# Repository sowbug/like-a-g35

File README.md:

Like A G35
==========

An alternate driver for GE Christmas lights that's an Arduino shield. Based on the 
[G35Arduino project](https://github.com/sowbug/G35Arduino). These instructions are 
for the G35 side of the board, built as of [tag v0.1](https://github.com/sowbug/like-a-g35/zipball/v0.1).

BOM
===

* The board. Have it manufactured by [OSH Park](http://oshpark.com/).
* A micro-USB connector, FCI part [10118193-0001LF](http://www.mouser.com/ProductDetail/FCI/10118193-0001LF/?qs=%2fha2pyFadujdGYiRLwYbSOKALiSo%252bepJVRcIj9hkdZjVBFUo3HGQQw%3d%3d).
* At least one [5.08MM 3-pin terminal block](http://www.mouser.com/ProductDetail/TE-Connectivity-AMP/282837-3/?qs=sGAEpiMZZMvlX3nhDDO4AEiipl7BG01uQiHyL2Oob2I%3d). The green things with screws.
* A bunch of snappable pin headers -- enough to make the usual Arduino 8/8/6/6 combo.
* Recommended: an Arduino, both for using with the shield, and during assembly as a frame for getting
the header pins straight.

Initial Usage
=============

1. Clone [G35Arduino](https://github.com/sowbug/G35Arduino) following the placement instructions there.
1. Fire up your Arduino IDE.
1. Change any of the examples to use pin 8 for the first strand, pin 9 for the second strand, and pin 10
if you're a big spender and have three G35 strands.
1. Program your Arduino.
1. Plug in the shield. Look for smoke. If you're more careful than I am, confirm that 5V is reading 5 volts,
GND is reading zero volts, and Data on the G1 header is putting out a digital signal.
1. Hook up the first strand of lights to the three-terminal header marked G1. Right before you cut off the
controller, as you were looking at the first light you saw +/D/-, left to right. See the
[V+/D/V- diagram](http://www.deepdarc.com/2010/11/27/hacking-christmas-lights/). Hook up + to 5V, the
middle wire to Data, and - to GND.
1. If you still have your Arduino plugged into your computer, by now you should be seeing at least the test
pattern on your strand. If not, check your wiring and assembly.

Production Usage
================

* The reason there is a USB connector on the shield is that the Arduino's power is limited to 500mA, or
else you risk blowing its polyfuse. Even a single G35 strand can use more than an amp. But the shield's USB
connector is a *direct* connection to the light power lines. So as long as you can find a power adapter
that fits the micro-USB plug (should be easy; lots of power adapters these days have type-A USB) and
provides regulated 5V, you can pump as much current as you want into this shield (it'll also power the
Arduino, of course). *BEWARE* that in exchange for this freedom, you can easily kill your lights and your
Arduino. You *must* provide *a regulated 5-volt supply*. Not 4.5, not 6, not 9, not 12. I don't care if your
7.5-volt supply worked fine with your Arduino. If you hook it up to this USB socket, all your hardware will
die and you might burn down your house.
* I've soldered the stranded copper wire of my lights so that they don't tarnish too much over the winter.

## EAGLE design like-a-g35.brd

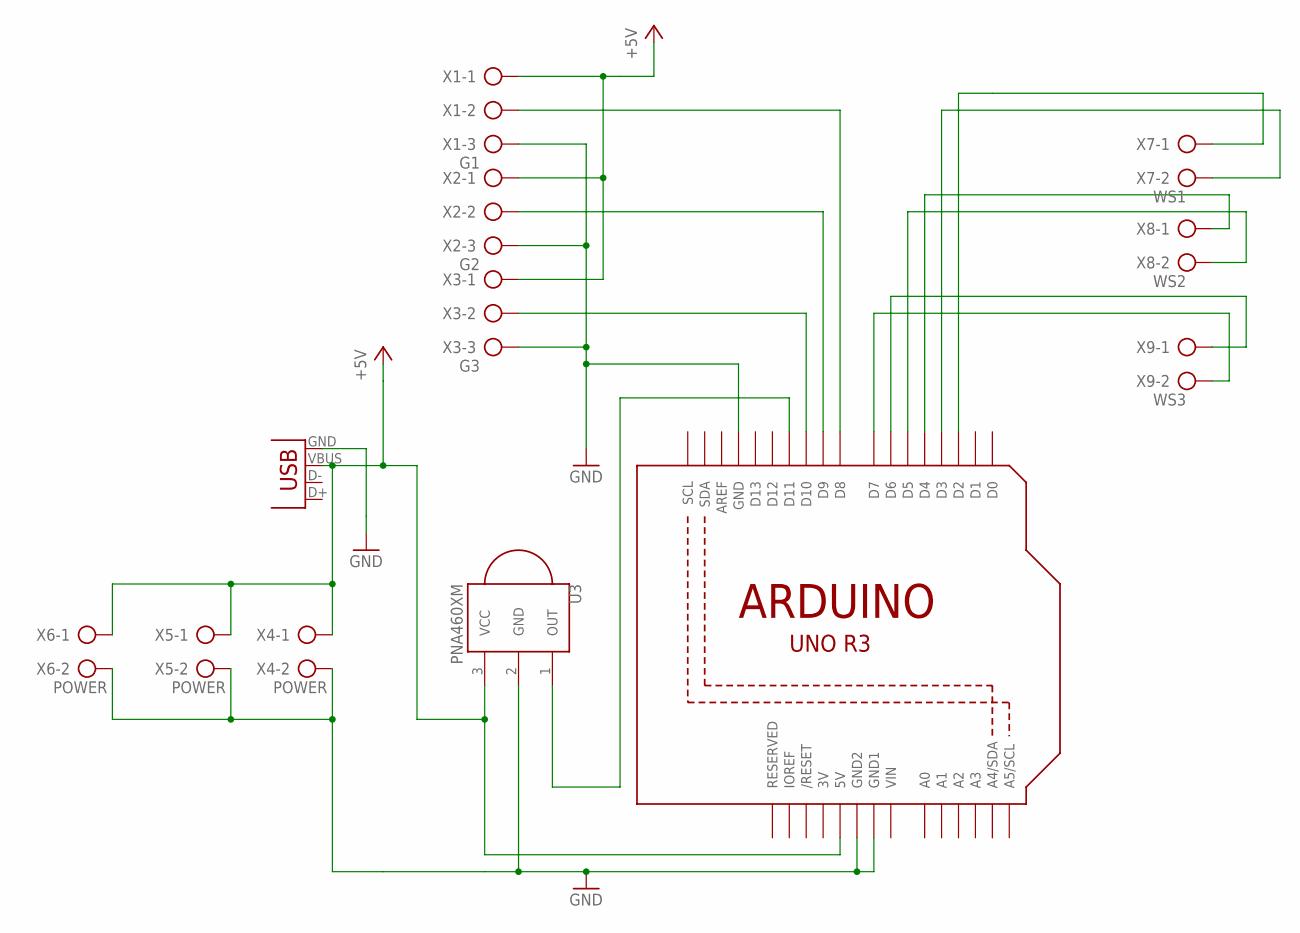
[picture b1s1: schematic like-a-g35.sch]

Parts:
U1: ARDUINOR3-DIMENSION; ARDUINOR3
U2: FCI_8193_MICRO_USB; FCI_MICRO_USB_8193
U3: PNA460XM
X1: G1; AK300/3
X2: G2; AK300/3
X3: G3; AK300/3
X4, X5, X6: POWER; AK300/2
X7: WS1; AK300/2
X8: WS2; AK300/2
X9: WS3; AK300/2

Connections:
3V: U1.3V
+5V: U1.5V, U2.VBUS, U3.3 (VCC), X1.1, X2.1, X3.1, X4.1, X5.1, X6.1
CLK1: U1.D3, X7.2
CLK2: U1.D5, X8.2
CLK3: U1.D7, X9.2
DATA1: U1.D2, X7.1
DATA2: U1.D4, X8.1
DATA3: U1.D6, X9.1
GDATA1: U1.D8, X1.2
GDATA2: U1.D9, X2.2
GDATA3: U1.D10, X3.2
GND: U1.GND, U1.GND1, U1.GND2, U2.GND, U3.2 (GND), X1.3, X2.3, X3.3, X4.2, X5.2, X6.2
IR-OUT: U1.D11, U3.1 (OUT)
VIN: U1.VIN

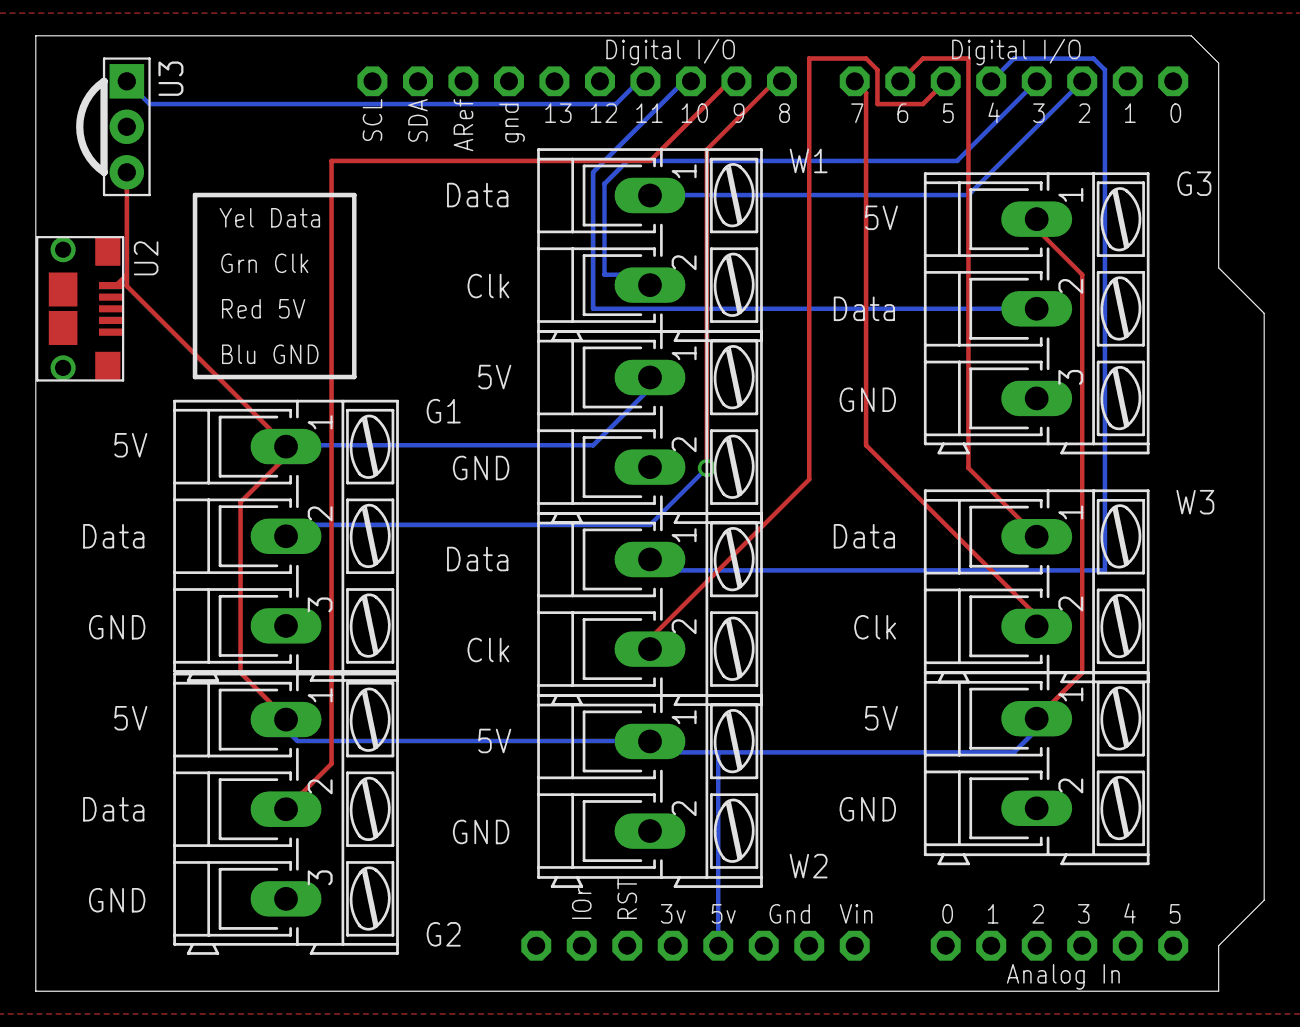
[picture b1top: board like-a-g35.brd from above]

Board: 2 copper layers, 68.6 x 53.3 mm, 12 parts (0 on the bottom side), 12 nets.

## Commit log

2012-05-24 New.
2012-09-11 0.9.
2012-09-11 Label each terminal block.
2012-09-11 Moved some labels around.
2012-09-11 Minor adjustments after previewing at OSH Park.
2012-10-10 Update README.md
    Real instructions for actual users.
